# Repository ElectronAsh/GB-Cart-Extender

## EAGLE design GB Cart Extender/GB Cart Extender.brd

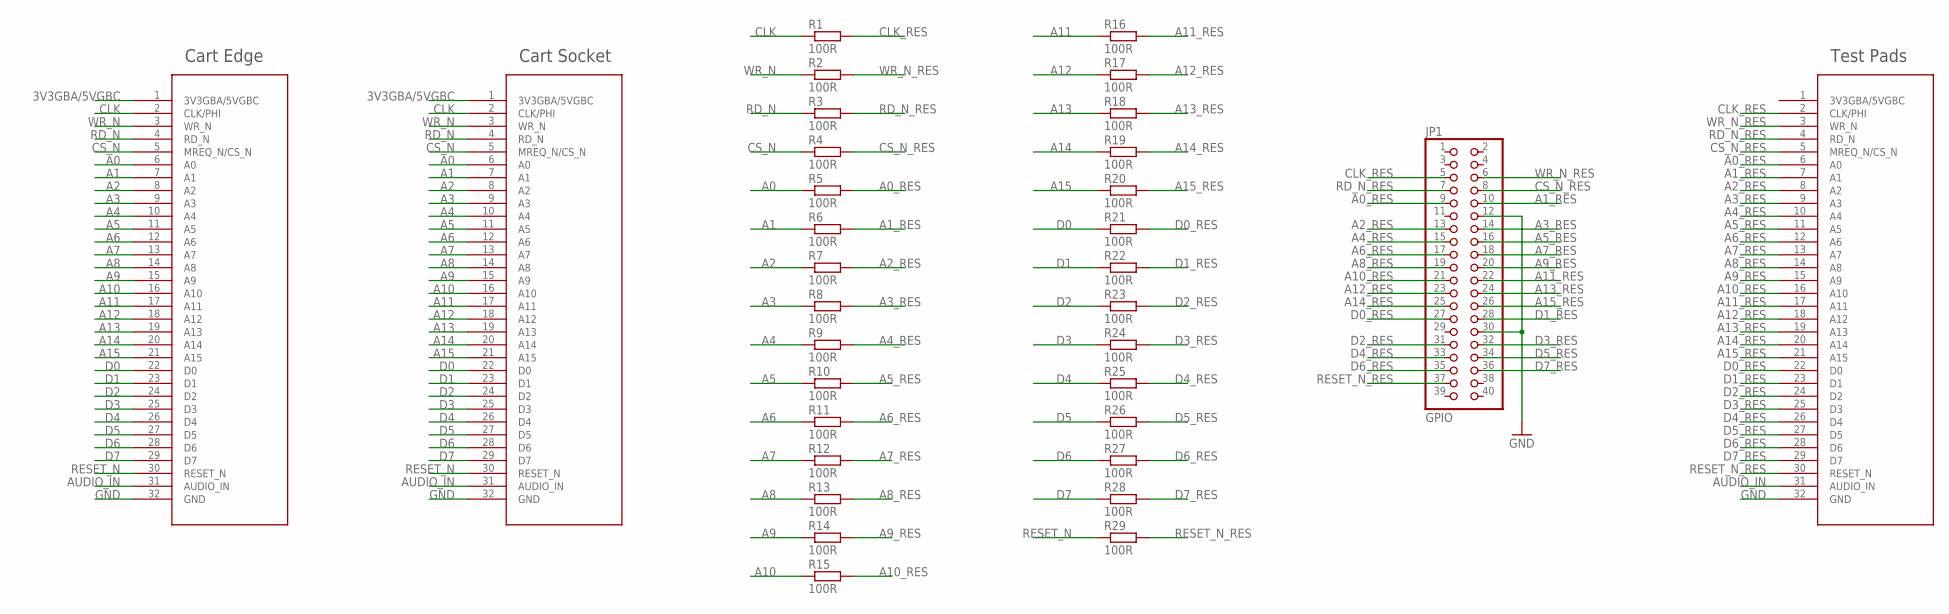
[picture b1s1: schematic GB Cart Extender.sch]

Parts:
EDGE: GB_CART_EDGE
JP1: GPIO; 2X20_SMT
PADS: GB_CART_SOCKET; GB_CART_1
R1, R2, R3, R4, R5, R6, R7, R8, R9, R10, R11, R12, R13, R14, R15, R16, R17, R18, R19, R20, R21, R22, R23, R24, R25, R26, R27, R28, R29: 100R; R0603
SOCKET: GB_CART_SOCKET; GB_CART_1

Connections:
3V3GBA/5VGBC: EDGE.1 (3V3GBA/5VGBC), SOCKET.1 (3V3GBA/5VGBC)
A0: EDGE.6 (A0), R5.1, SOCKET.6 (A0)
A0_RES: JP1.9, PADS.6 (A0), R5.2
A1: EDGE.7 (A1), R6.1, SOCKET.7 (A1)
A1_RES: JP1.10, PADS.7 (A1), R6.2
A2: EDGE.8 (A2), R7.1, SOCKET.8 (A2)
A2_RES: JP1.13, PADS.8 (A2), R7.2
A3: EDGE.9 (A3), R8.1, SOCKET.9 (A3)
A3_RES: JP1.14, PADS.9 (A3), R8.2
A4: EDGE.10 (A4), R9.1, SOCKET.10 (A4)
A4_RES: JP1.15, PADS.10 (A4), R9.2
A5: EDGE.11 (A5), R10.1, SOCKET.11 (A5)
A5_RES: JP1.16, PADS.11 (A5), R10.2
A6: EDGE.12 (A6), R11.1, SOCKET.12 (A6)
A6_RES: JP1.17, PADS.12 (A6), R11.2
A7: EDGE.13 (A7), R12.1, SOCKET.13 (A7)
A7_RES: JP1.18, PADS.13 (A7), R12.2
A8: EDGE.14 (A8), R13.1, SOCKET.14 (A8)
A8_RES: JP1.19, PADS.14 (A8), R13.2
A9: EDGE.15 (A9), R14.1, SOCKET.15 (A9)
A9_RES: JP1.20, PADS.15 (A9), R14.2
A10: EDGE.16 (A10), R15.1, SOCKET.16 (A10)
A10_RES: JP1.21, PADS.16 (A10), R15.2
A11: EDGE.17 (A11), R16.1, SOCKET.17 (A11)
A11_RES: JP1.22, PADS.17 (A11), R16.2
A12: EDGE.18 (A12), R17.1, SOCKET.18 (A12)
A12_RES: JP1.23, PADS.18 (A12), R17.2
A13: EDGE.19 (A13), R18.1, SOCKET.19 (A13)
A13_RES: JP1.24, PADS.19 (A13), R18.2
A14: EDGE.20 (A14), R19.1, SOCKET.20 (A14)
A14_RES: JP1.25, PADS.20 (A14), R19.2
A15: EDGE.21 (A15), R20.1, SOCKET.21 (A15)
A15_RES: JP1.26, PADS.21 (A15), R20.2
AUDIO_IN: EDGE.31 (AUDIO_IN), PADS.31 (AUDIO_IN), SOCKET.31 (AUDIO_IN)
CLK: EDGE.2 (CLK/PHI), R1.1, SOCKET.2 (CLK/PHI)
CLK_RES: JP1.5, PADS.2 (CLK/PHI), R1.2
CS_N: EDGE.5 (MREQ_N/CS_N), R4.1, SOCKET.5 (MREQ_N/CS_N)
CS_N_RES: JP1.8, PADS.5 (MREQ_N/CS_N), R4.2
D0: EDGE.22 (D0), R21.1, SOCKET.22 (D0)
D0_RES: JP1.27, PADS.22 (D0), R21.2
D1: EDGE.23 (D1), R22.1, SOCKET.23 (D1)
D1_RES: JP1.28, PADS.23 (D1), R22.2
D2: EDGE.24 (D2), R23.1, SOCKET.24 (D2)
D2_RES: JP1.31, PADS.24 (D2), R23.2
D3: EDGE.25 (D3), R24.1, SOCKET.25 (D3)
D3_RES: JP1.32, PADS.25 (D3), R24.2
D4: EDGE.26 (D4), R25.1, SOCKET.26 (D4)
D4_RES: JP1.33, PADS.26 (D4), R25.2
D5: EDGE.27 (D5), R26.1, SOCKET.27 (D5)
D5_RES: JP1.34, PADS.27 (D5), R26.2
D6: EDGE.28 (D6), R27.1, SOCKET.28 (D6)
D6_RES: JP1.35, PADS.28 (D6), R27.2
D7: EDGE.29 (D7), R28.1, SOCKET.29 (D7)
D7_RES: JP1.36, PADS.29 (D7), R28.2
GND: EDGE.32 (GND), JP1.12, JP1.30, PADS.32 (GND), SOCKET.32 (GND)
RD_N: EDGE.4 (RD_N), R3.1, SOCKET.4 (RD_N)
RD_N_RES: JP1.7, PADS.4 (RD_N), R3.2
RESET_N: EDGE.30 (RESET_N), R29.1, SOCKET.30 (RESET_N)
RESET_N_RES: JP1.37, PADS.30 (RESET_N), R29.2
WR_N: EDGE.3 (WR_N), R2.1, SOCKET.3 (WR_N)
WR_N_RES: JP1.6, PADS.3 (WR_N), R2.2

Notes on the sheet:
Cart Edge
Cart Socket
Test Pads

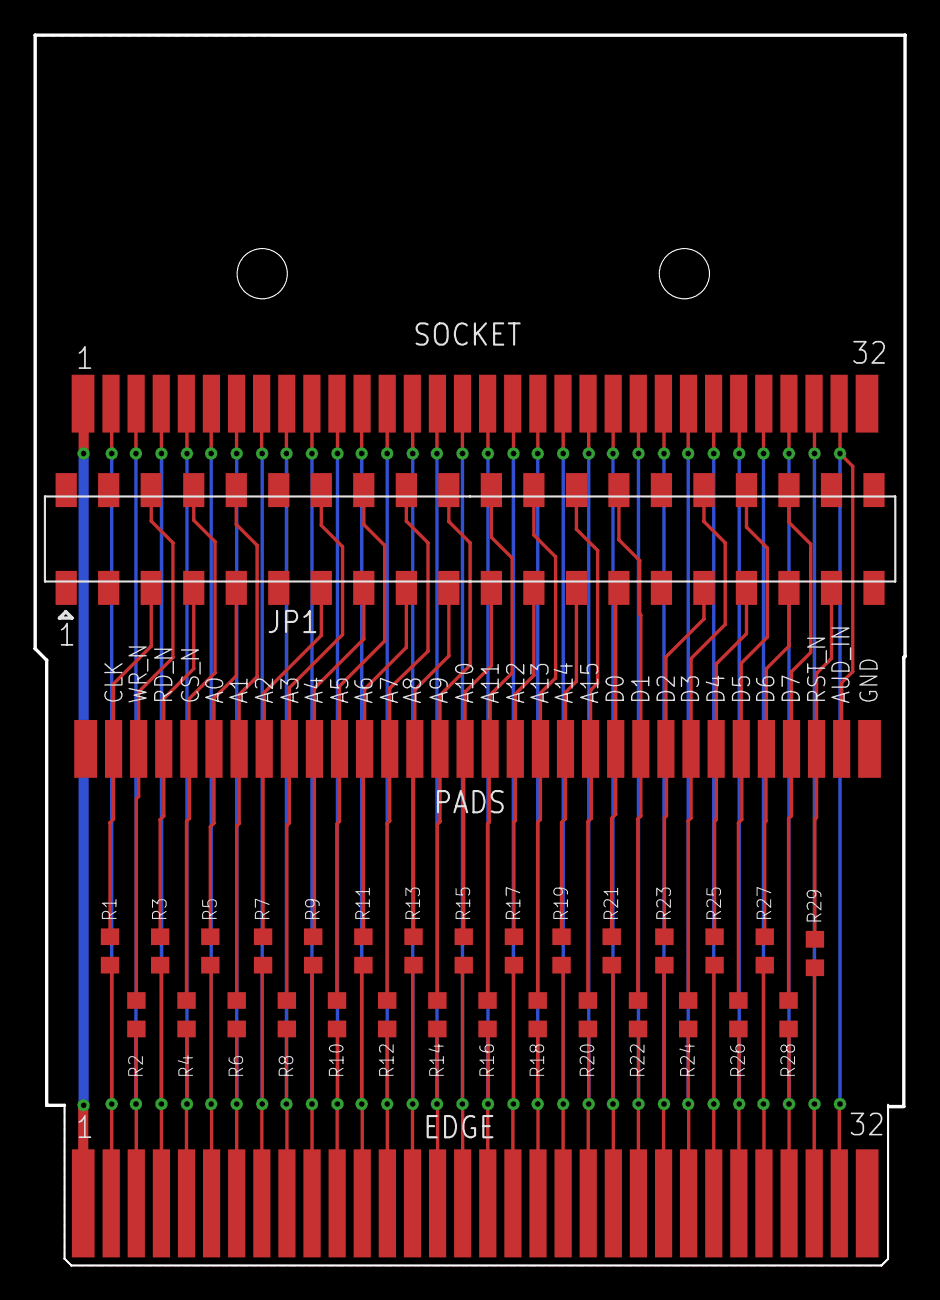
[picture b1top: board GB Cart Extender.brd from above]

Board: 2 copper layers, 52.0 x 73.5 mm, 33 parts (0 on the bottom side), 61 nets.
